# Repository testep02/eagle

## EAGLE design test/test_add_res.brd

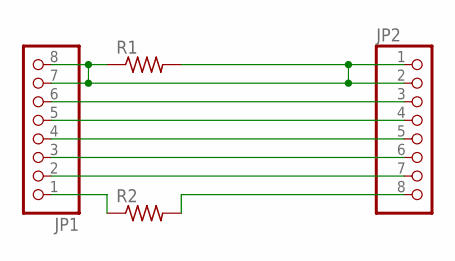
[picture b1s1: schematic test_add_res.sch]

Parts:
JP1, JP2: PINHD-1X8; 1X08
R1, R2: R-US_R0805; R0805

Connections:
unnamed: JP1.7, JP1.8, JP2.1, JP2.2, R1.1, R1.2
unnamed: JP1.6, JP2.3
unnamed: JP1.5, JP2.4
unnamed: JP1.4, JP2.5
unnamed: JP1.3, JP2.6
unnamed: JP1.2, JP2.7
unnamed: JP2.8, R2.2
unnamed: JP1.1, R2.1

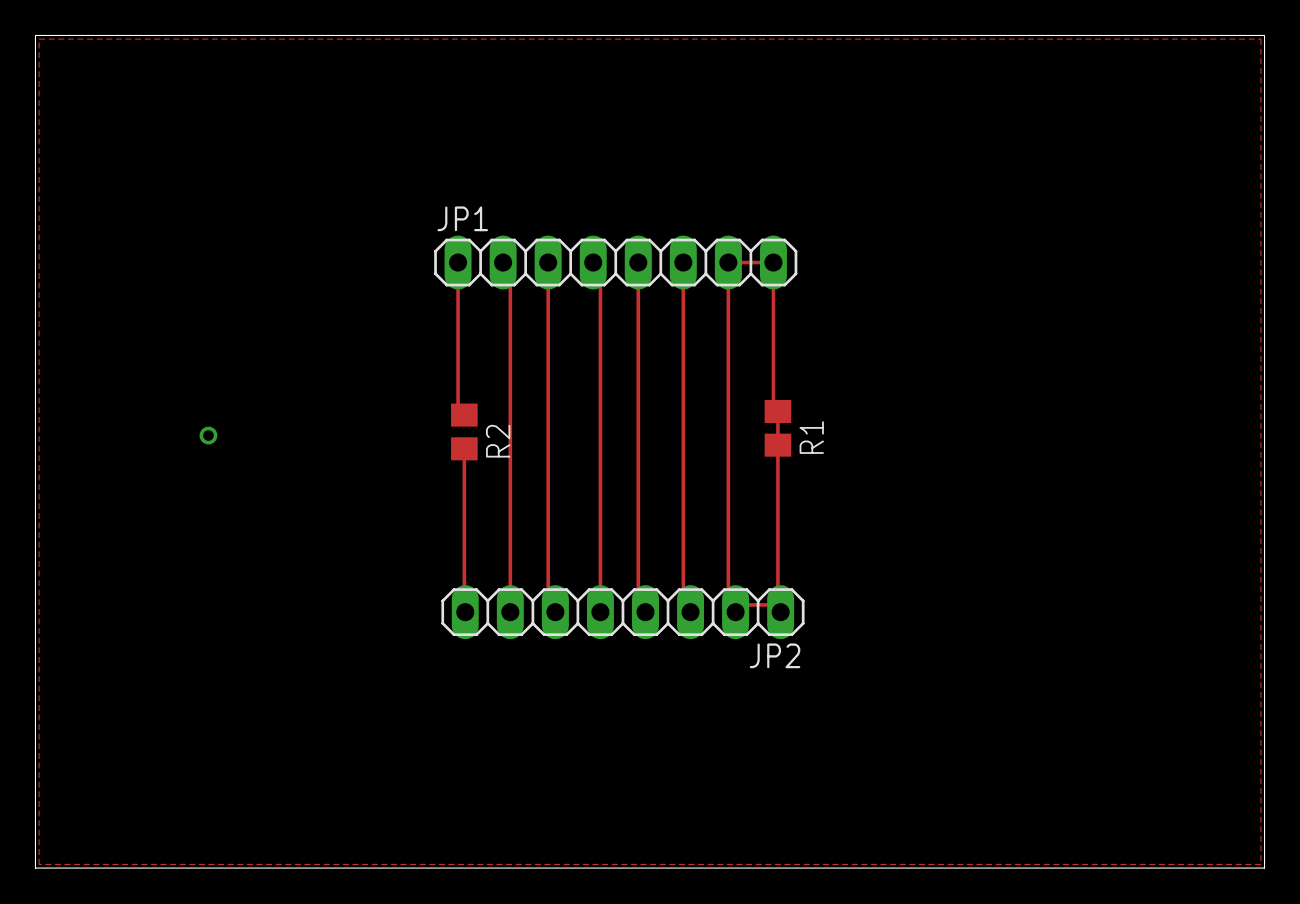
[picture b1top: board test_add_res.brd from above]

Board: 4 copper layers, 69.3 x 46.9 mm, 4 parts (0 on the bottom side), 8 nets.
